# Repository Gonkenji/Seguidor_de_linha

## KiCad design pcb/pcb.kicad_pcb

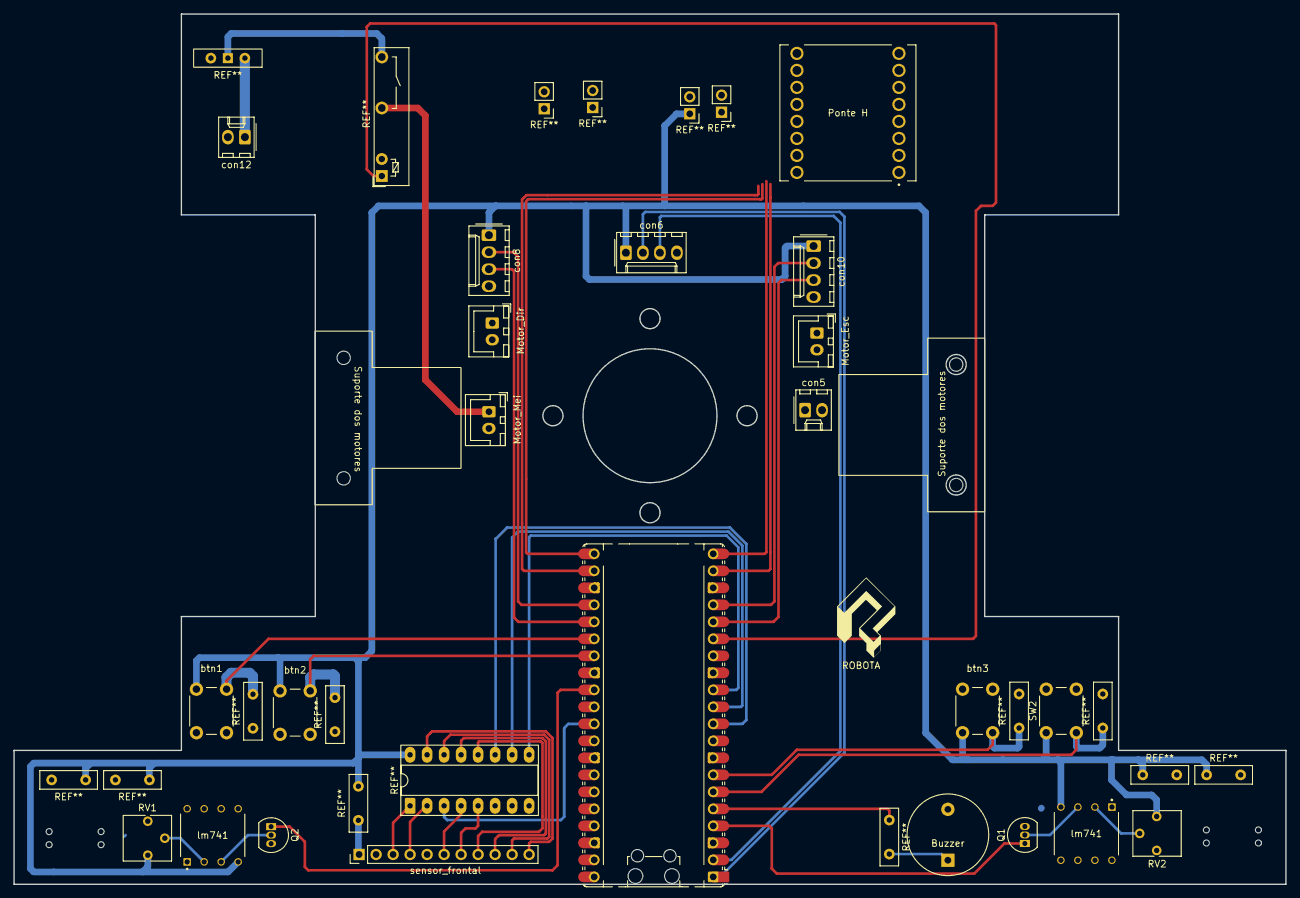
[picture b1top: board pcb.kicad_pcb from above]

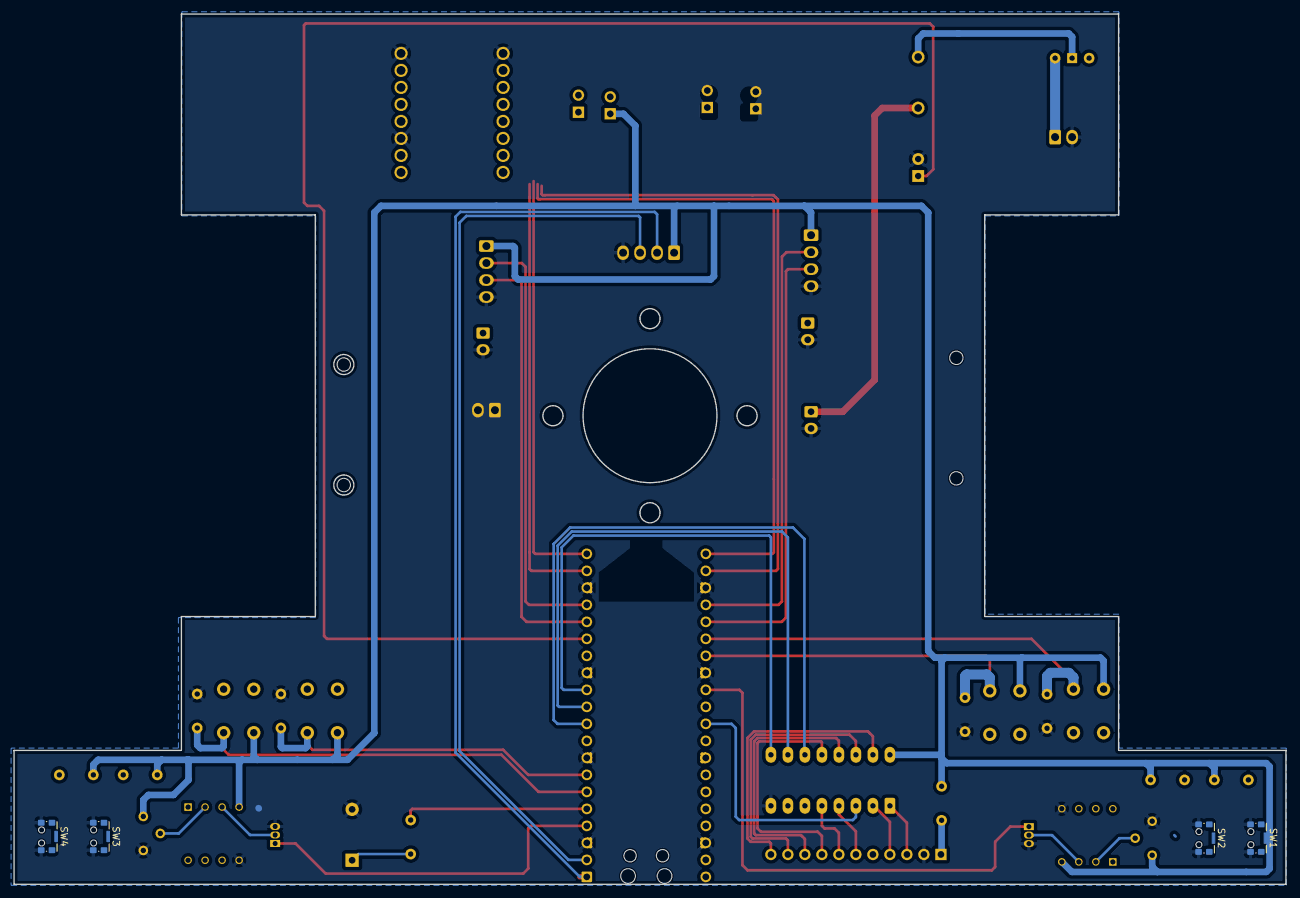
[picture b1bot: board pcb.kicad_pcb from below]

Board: 2 copper layers, 190.0 x 130.0 mm, 28 parts (4 on the bottom side), 19 nets.

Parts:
A1: RaspberryPi_Pico; RaspberryPi_Pico_Common_Unspecified
BZ1: Buzzer; Buzzer_12x9.5RM7.6
Motor_direito1: Conn_01x02_Socket; JST_XH_B2B-XH-A_1x02_P2.50mm_Vertical
Q1, Q2: BC547; TO-92_Inline
RV1, RV2: trimpot_10k; Potentiometer_Vishay_T73YP_Vertical
SW1, SW2#5, SW3, SW4: CK_KMS2xxG; SW_SPST_CK_KMS2xxGP
SW2: btn2; SW_PUSH_6mm
SW2#2: btn1; SW_PUSH_6mm
SW2#3: btn4; SW_PUSH_6mm
SW2#4: btn3; SW_PUSH_6mm
Suporte dos motores: suporte
Suporte dos motores#2: suporte
U6: ROB-14450; MODULE_ROB-14450
U9, U9#2: lm741; DIP794W45P254L959H508Q8
con4: MOTOR2; JST_XH_B2B-XH-A_1x02_P2.50mm_Vertical
con5: MOTOR1; Molex_KK-254_AE-6410-02A_1x02_P2.54mm_Vertical
con6: GIROSCOPIO; Molex_KK-254_AE-6410-04A_1x04_P2.54mm_Vertical
con8: ENC1; Molex_KK-254_AE-6410-04A_1x04_P2.54mm_Vertical
con10: ENC2; Molex_KK-254_AE-6410-04A_1x04_P2.54mm_Vertical
con12: Bateria; Molex_KK-254_AE-6410-02A_1x02_P2.54mm_Vertical
cont11: MOTOR3; JST_XH_B2B-XH-A_1x02_P2.50mm_Vertical
sensor_frontal1: Conn_01x11_Socket; PinHeader_1x11_P2.54mm_Vertical

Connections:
+3V3: RV1.1, RV2.1, SW1.1, SW2.1, SW2#2.1, SW2#3.1, SW2#4.1, SW2#5.1, SW3.1, SW4.1, U9.4 (V+), U9#2.4 (V+), con6.1, con8.1, con10.1, sensor_frontal1.1
BTN0: A1.6 (GPIO4), SW1.SH (B), SW2#3.2
BTN1: A1.7 (GPIO5), SW2#4.2
BTN2: A1.27 (GPIO21), SW2.2, SW3.SH (B)
BTN3: A1.26 (GPIO20), SW2#2.3 (2), SW4.SH (B)
BZR: A1.5 (GPIO3), BZ1.1 (-)
ENC11: A1.24 (GPIO18), con8.2
ENC12: A1.25 (GPIO19), con8.3
ENC21: A1.17 (GPIO13), con10.2
ENC22: A1.16 (GPIO12), con10.3
GND: A1.3 (GND), A1.8 (GND), A1.13 (GND), A1.18 (GND), A1.23 (GND), A1.28 (GND), A1.38 (GND), BZ1.2 (+), Q1.3 (E), Q2.3 (E), RV1.3, RV2.3, SW1.2, SW2#5.2, SW3.2, SW4.2, U6.3 (GND), U6.8 (GND), U6.9 (GND), U9.5 (V-), U9#2.5 (V-), con6.4, con8.4, con10.4, con12.2, cont11.2, sensor_frontal1.2
GSDA: A1.1 (GPIO0), con6.2
GSDL: A1.2 (GPIO1), con6.3
unnamed: Q1.2 (B), U9#2.3
unnamed: Q2.2 (B), U9.3
unnamed: RV1.2, U9.2 (-)
unnamed: RV2.2, U9#2.2 (-)
SLD: A1.29 (GPIO22), Q2.1 (C)
SLE: A1.4 (GPIO2), Q1.1 (C)

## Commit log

2025-10-03 Create sensorlinha
2025-10-07 Create testesensor
2025-10-09 Create Calibragem
2025-10-09 calibragem e codigo limpo
2025-10-09 Organização
2025-10-24 Controle on off
    controle on off não generalizado, para controle P generalizar
2025-10-28 controleP incompleto
2025-11-15 Update Controle_PID_W.ino
    Funcionando mas sem parar
2025-11-15 Update Controle_PID_W.ino
    timeando
2026-01-31 Divisão de seguidores de linha
    Separando o seguidor de linha da competição interna com o novo seguidor de linha
2026-01-31 codigo legado movido e adicionado documentação
